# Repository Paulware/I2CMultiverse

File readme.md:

I2C Multiverse

<ul>
<li>Purpose<br>
  The purpose of the I2C Multiverse is to create lego-like components that 
can easily be added or removed from a project.  Each component will communicate
with the master using I2C (pronounced I-Squared-C).  
</li>
<li>  
Form<br>
  Each component will be follow the form of an Arduino shield, but the 
only pins that are passed to each shield are 5V, GND, SDA (A4) and SCL (A5).
Within each component are 2 atmega328s:
  <ul>
  <li>communicate with the rest of the system using I2C</li>
  <li>communicate with the component which can also be a shield</li>
  </ul>
</li>
<li>  
Components<br>
  <ul>
  <li>Ultrasonic distance measuring device using US-020 (7 meter range)</li>
  <li>HBridge control to drive 2 L298s</li>
</li>
<li>
Schematics<br>
  <ul>
  <li>Dual Atmega 328s which are the heart of each component</li>
  </ul>
</li>
<li>
Sketches<br>
  <ul>
  <li>TBD</li>
  </ul>
</li>
<li>
Images</br>
  <ul>
  <li>TBD</li>
  </ul>
</li>
</ul>
  
Questions/Comments<br>
  paulware@hotmail.com
<p>  
Help with projects<br>
  [I help on Fiverr](http://fiverr.com/paulware/help-with-your-arduino-project)
<p>

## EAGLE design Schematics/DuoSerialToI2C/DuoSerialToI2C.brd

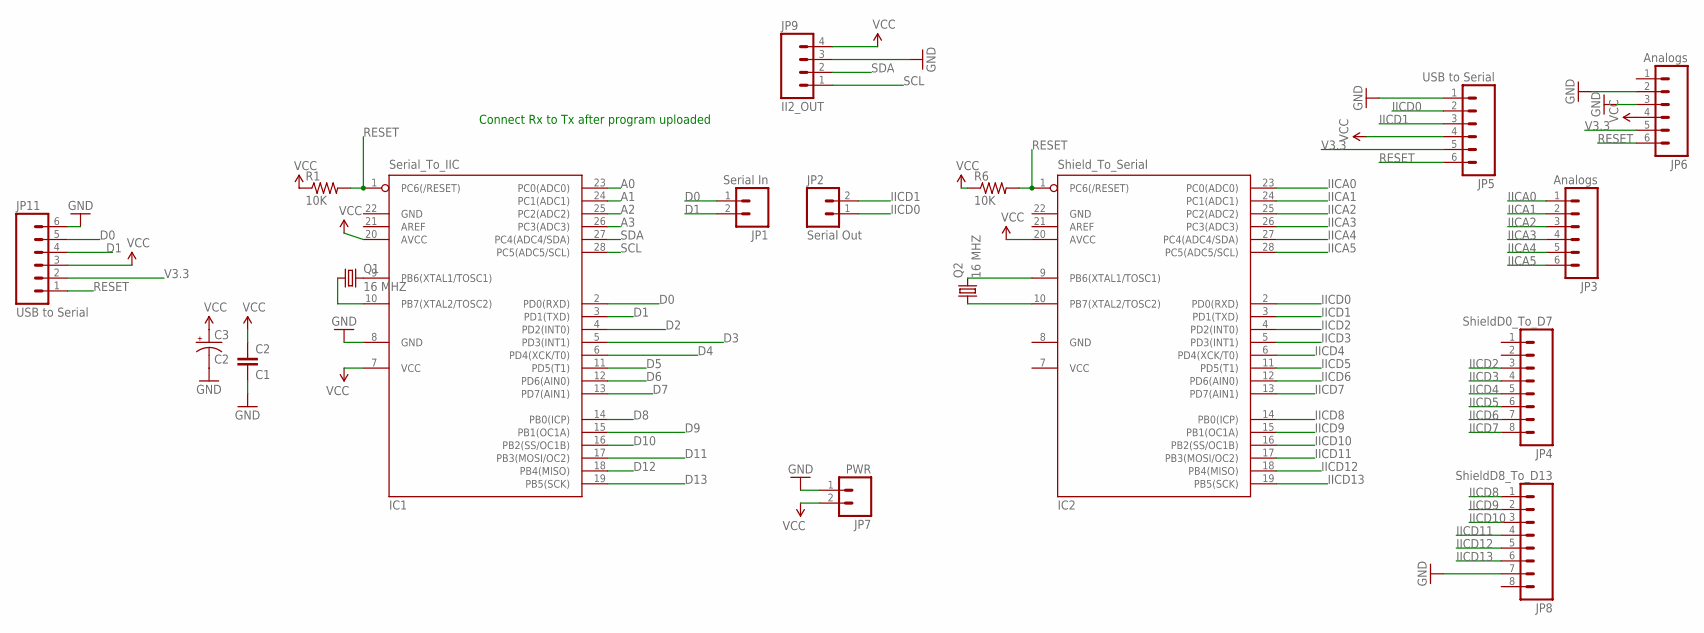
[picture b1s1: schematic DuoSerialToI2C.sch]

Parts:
C2: C1; CAP-PTH-SMALL
C3: C2; CPOL-RADIAL-100UF-25V
IC1: Serial_To_IIC; DIL28-3
IC2: Shield_To_Serial; DIL28-3
JP1: Serial In; 1X02
JP2: Serial Out; 1X02
JP3, JP6: Analogs; 1X06
JP4: ShieldD0_To_D7; 1X08
JP5, JP11: USB to Serial; 1X06
JP7: PWR; 1X02
JP8: ShieldD8_To_D13; 1X08
JP9: II2_OUT; 1X04_LONGPADS
Q1, Q2: 16 MHZ; HC49US
R1, R6: 10K; AXIAL-0.3

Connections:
A0: IC1.23 (PC0(ADC0))
A1: IC1.24 (PC1(ADC1))
A2: IC1.25 (PC2(ADC2))
A3: IC1.26 (PC3(ADC3))
D0: IC1.2 (PD0(RXD)), JP1.1, JP11.5
D1: IC1.3 (PD1(TXD)), JP1.2, JP11.4
D2: IC1.4 (PD2(INT0))
D3: IC1.5 (PD3(INT1))
D4: IC1.6 (PD4(XCK/T0))
D5: IC1.11 (PD5(T1))
D6: IC1.12 (PD6(AIN0))
D7: IC1.13 (PD7(AIN1))
D8: IC1.14 (PB0(ICP))
D9: IC1.15 (PB1(OC1A))
D10: IC1.16 (PB2(SS/OC1B))
D11: IC1.17 (PB3(MOSI/OC2))
D12: IC1.18 (PB4(MISO))
D13: IC1.19 (PB5(SCK))
GND: C2.2, C3.2 (-), IC1.8 (GND), IC1.22 (GND), IC2.8 (GND), IC2.22 (GND), JP5.1, JP6.2, JP6.3, JP7.1, JP8.7, JP9.3, JP11.6
IICA0: IC2.23 (PC0(ADC0)), JP3.1
IICA1: IC2.24 (PC1(ADC1)), JP3.2
IICA2: IC2.25 (PC2(ADC2)), JP3.3
IICA3: IC2.26 (PC3(ADC3)), JP3.4
IICA4: IC2.27 (PC4(ADC4/SDA)), JP3.5
IICA5: IC2.28 (PC5(ADC5/SCL)), JP3.6
IICD0: IC2.2 (PD0(RXD)), JP2.1, JP5.2
IICD1: IC2.3 (PD1(TXD)), JP2.2, JP5.3
IICD2: IC2.4 (PD2(INT0)), JP4.3
IICD3: IC2.5 (PD3(INT1)), JP4.4
IICD4: IC2.6 (PD4(XCK/T0)), JP4.5
IICD5: IC2.11 (PD5(T1)), JP4.6
IICD6: IC2.12 (PD6(AIN0)), JP4.7
IICD7: IC2.13 (PD7(AIN1)), JP4.8
IICD8: IC2.14 (PB0(ICP)), JP8.1
IICD9: IC2.15 (PB1(OC1A)), JP8.2
IICD10: IC2.16 (PB2(SS/OC1B)), JP8.3
IICD11: IC2.17 (PB3(MOSI/OC2)), JP8.4
IICD12: IC2.18 (PB4(MISO)), JP8.5
IICD13: IC2.19 (PB5(SCK)), JP8.6
unnamed: IC2.9 (PB6(XTAL1/TOSC1)), Q2.2
unnamed: IC2.10 (PB7(XTAL2/TOSC2)), Q2.1
unnamed: IC1.9 (PB6(XTAL1/TOSC1)), Q1.2
unnamed: IC1.10 (PB7(XTAL2/TOSC2)), Q1.1
RESET: IC1.1 (PC6(/RESET)), IC2.1 (PC6(/RESET)), JP5.6, JP6.6, JP11.1, R1.P$2 (2), R6.P$2 (2)
SCL: IC1.28 (PC5(ADC5/SCL)), JP9.1
SDA: IC1.27 (PC4(ADC4/SDA)), JP9.2
V3.3: JP5.5, JP6.5, JP11.2
VCC: C2.1, C3.1 (+), IC1.7 (VCC), IC1.20 (AVCC), IC2.7 (VCC), IC2.20 (AVCC), JP5.4, JP6.4, JP7.2, JP9.4, JP11.3, R1.P$1 (1), R6.P$1 (1)

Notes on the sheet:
Connect Rx to Tx after program uploaded

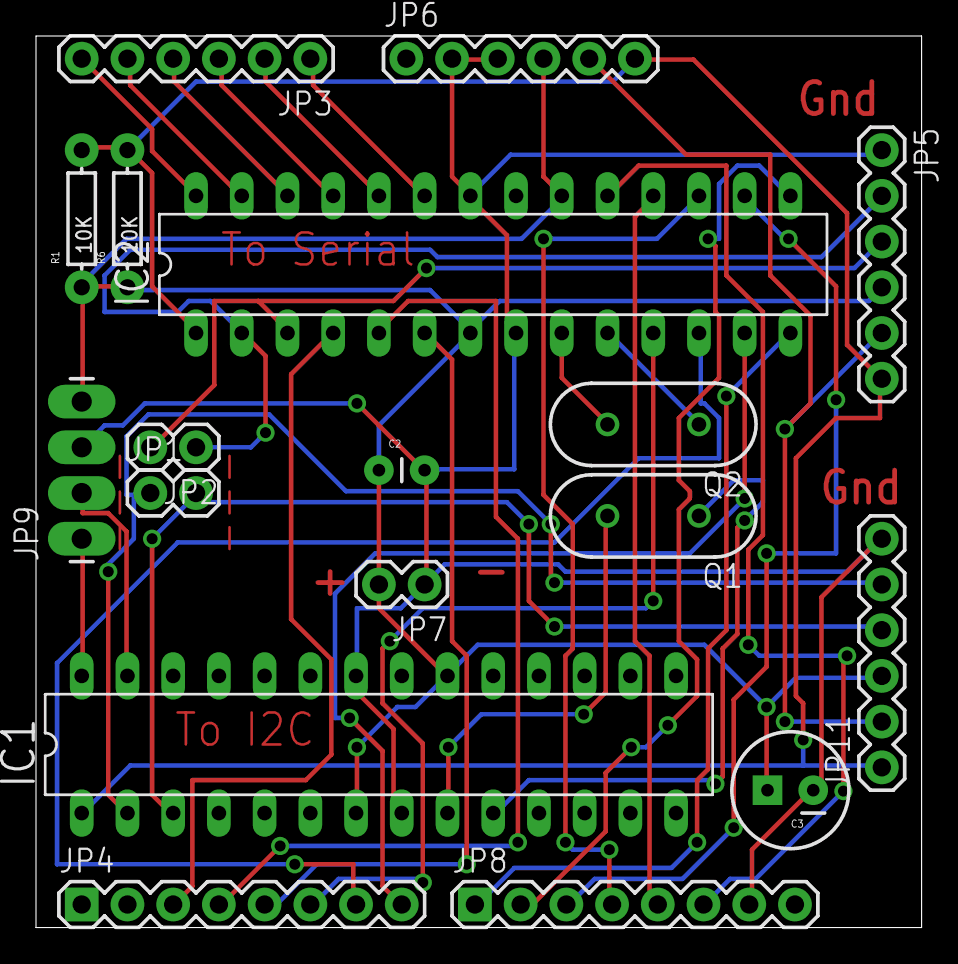
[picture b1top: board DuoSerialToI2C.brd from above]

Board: 2 copper layers, 49.2 x 49.5 mm, 18 parts (0 on the bottom side), 32 nets.

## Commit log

2013-03-15 V0.01
    Initial Creation
2013-03-15 v0.02
    Modified readm.md

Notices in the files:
parts and their libraries:
SparkFun-Connectors: Licensing: CC v3.0 Share-Alike You are welcome to use this library for commercial purposes.
